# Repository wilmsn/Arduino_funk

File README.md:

# Arduino_funk
A simple PCB for ATMEGA328 and nrf24l01

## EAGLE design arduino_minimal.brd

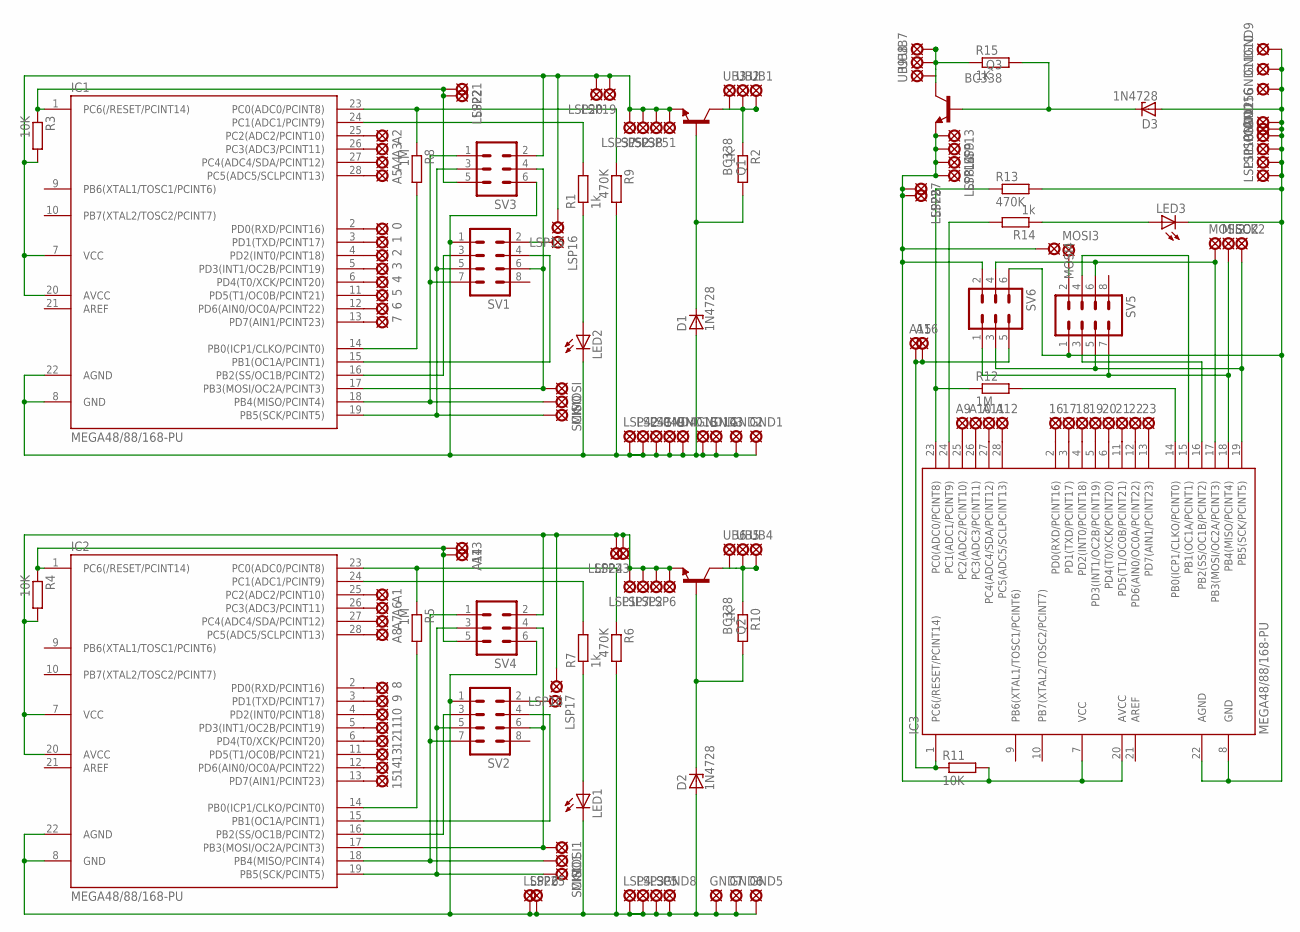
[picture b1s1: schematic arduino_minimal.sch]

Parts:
0, 1, 2, 3, 4, 5, 6, 7, 8, 9, 10, 11, 12, 13, 14, 15, 16, 17, 18, 19, 20, 21, 22, 23: LSP10
A1, A2, A3, A4, A5, A6, A7, A8, A9, A10, A11, A12, A13, A14, A15, A16: LSP10
D1, D2, D3: 1N4728; DO41Z10
GND1, GND2, GND3, GND4, GND5, GND6, GND7, GND8, GND9, GND10, GND11, GND12, GND13, GND14, GND15, GND16: LSP10
IC1, IC2, IC3: MEGA48/88/168-PU; DIL28-3
LED1, LED2, LED3: LED3MM
LSP1, LSP2, LSP3, LSP4, LSP5, LSP6, LSP7, LSP8, LSP9, LSP10, LSP11, LSP12, LSP13, LSP14, LSP15, LSP16, LSP17, LSP18, LSP19, LSP20, LSP21, LSP22, LSP23, LSP24, LSP25, LSP26, LSP27, LSP28, LSP37, LSP38, LSP41, LSP42, LSP49, LSP51, LSP52: LSP10
MISO, MISO1, MISO2: LSP10
MOSI, MOSI1, MOSI2, MOSI3, MOSI4: LSP10
Q1, Q2, Q3: BC338; TO92-EBC
R1, R7, R14: 1k; 0204/7
R2, R10, R15: 1K; 0204/7
R3, R4, R11: 10K; 0204/7
R5, R8, R12: 1M; 0204/7
R6, R9, R13: 470K; 0204/7
SCK, SCK1, SCK2: LSP10
SV1, SV2, SV5: MA04-2
SV3, SV4, SV6: MA03-2
UB1, UB2, UB3, UB4, UB5, UB6, UB7, UB8, UB9: LSP10

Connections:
CE1: IC1.16 (PB2(SS/OC1B/PCINT2)), SV1.3
CSN1: IC1.15 (PB1(OC1A/PCINT1)), SV1.4
GND: D1.A, GND1.MP, GND2.MP, GND3.MP, GND4.MP, GND13.MP, GND14.MP, IC1.8 (GND), IC1.22 (AGND), LED2.K (C), LSP41.MP, LSP42.MP, LSP49.MP, R9.2, SV1.1, SV3.6
MISO1: IC1.18 (PB4(MISO/PCINT4)), MISO.MP, SV1.7, SV3.1
MOSI1: IC1.17 (PB3(MOSI/OC2A/PCINT3)), MOSI.MP, SV1.6, SV3.4
unnamed: A13.MP, A14.MP, IC2.1 (PC6(/RESET/PCINT14)), R4.1, SV4.5
unnamed: LSP16.MP, SV1.2
unnamed: IC1.14 (PB0(ICP1/CLKO/PCINT0)), R8.2
unnamed: IC2.14 (PB0(ICP1/CLKO/PCINT0)), R5.2
unnamed: IC1.23 (PC0(ADC0/PCINT8)), R8.1, R9.1
unnamed: IC2.23 (PC0(ADC0/PCINT8)), R5.1, R6.1
unnamed: IC2.24 (PC1(ADC1/PCINT9)), R7.2
unnamed: LED1.A, R7.1
unnamed: IC1.24 (PC1(ADC1/PCINT9)), R1.2
unnamed: LED2.A, R1.1
unnamed: IC2.15 (PB1(OC1A/PCINT1)), SV2.4
unnamed: IC2.16 (PB2(SS/OC1B/PCINT2)), SV2.3
unnamed: IC2.17 (PB3(MOSI/OC2A/PCINT3)), MOSI1.MP, SV2.6, SV4.4
unnamed: IC2.18 (PB4(MISO/PCINT4)), MISO1.MP, SV2.7, SV4.1
unnamed: IC2.19 (PB5(SCK/PCINT5)), SCK1.MP, SV2.5, SV4.3
unnamed: LSP17.MP, SV2.2
unnamed: MOSI3.MP, SV5.2
unnamed: 15.MP, IC2.13 (PD7(AIN1/PCINT23))
unnamed: 14.MP, IC2.12 (PD6(AIN0/OC0A/PCINT22))
unnamed: 13.MP, IC2.11 (PD5(T1/OC0B/PCINT21))
unnamed: 12.MP, IC2.6 (PD4(T0/XCK/PCINT20))
unnamed: 11.MP, IC2.5 (PD3(INT1/OC2B/PCINT19))
unnamed: 10.MP, IC2.4 (PD2(INT0/PCINT18))
unnamed: 9.MP, IC2.3 (PD1(TXD/PCINT17))
unnamed: 8.MP, IC2.2 (PD0(RXD/PCINT16))
unnamed: A1.MP, IC2.25 (PC2(ADC2/PCINT10))
unnamed: A6.MP, IC2.26 (PC3(ADC3/PCINT11))
unnamed: A7.MP, IC2.27 (PC4(ADC4/SDA/PCINT12))
unnamed: A8.MP, IC2.28 (PC5(ADC5/SCLPCINT13))
unnamed: 7.MP, IC1.13 (PD7(AIN1/PCINT23))
unnamed: 6.MP, IC1.12 (PD6(AIN0/OC0A/PCINT22))
unnamed: 5.MP, IC1.11 (PD5(T1/OC0B/PCINT21))
unnamed: 4.MP, IC1.6 (PD4(T0/XCK/PCINT20))
unnamed: 3.MP, IC1.5 (PD3(INT1/OC2B/PCINT19))
unnamed: 2.MP, IC1.4 (PD2(INT0/PCINT18))
unnamed: 1.MP, IC1.3 (PD1(TXD/PCINT17))
unnamed: 0.MP, IC1.2 (PD0(RXD/PCINT16))
unnamed: A2.MP, IC1.25 (PC2(ADC2/PCINT10))
unnamed: A3.MP, IC1.26 (PC3(ADC3/PCINT11))
unnamed: A4.MP, IC1.27 (PC4(ADC4/SDA/PCINT12))
unnamed: A5.MP, IC1.28 (PC5(ADC5/SCLPCINT13))
unnamed: D2.A, GND5.MP, GND6.MP, GND7.MP, GND8.MP, IC2.8 (GND), IC2.22 (AGND), LED1.K (C), LSP3.MP, LSP4.MP, LSP5.MP, LSP25.MP, LSP26.MP, R6.2, SV2.1, SV4.6
unnamed: Q1.C, R2.1, UB1.MP, UB2.MP, UB3.MP
unnamed: D1.C, Q1.B, R2.2
unnamed: Q2.C, R10.1, UB4.MP, UB5.MP, UB6.MP
unnamed: D2.C, Q2.B, R10.2
unnamed: A15.MP, A16.MP, IC3.1 (PC6(/RESET/PCINT14)), R11.1, SV6.5
unnamed: IC3.14 (PB0(ICP1/CLKO/PCINT0)), R12.2
unnamed: IC3.23 (PC0(ADC0/PCINT8)), R12.1, R13.1
unnamed: IC3.24 (PC1(ADC1/PCINT9)), R14.2
unnamed: LED3.A, R14.1
unnamed: IC3.15 (PB1(OC1A/PCINT1)), SV5.4
unnamed: IC3.16 (PB2(SS/OC1B/PCINT2)), SV5.3
unnamed: IC3.17 (PB3(MOSI/OC2A/PCINT3)), MOSI2.MP, SV5.6, SV6.4
unnamed: IC3.18 (PB4(MISO/PCINT4)), MISO2.MP, SV5.7, SV6.1
unnamed: IC3.19 (PB5(SCK/PCINT5)), SCK2.MP, SV5.5, SV6.3
unnamed: 23.MP, IC3.13 (PD7(AIN1/PCINT23))
unnamed: 22.MP, IC3.12 (PD6(AIN0/OC0A/PCINT22))
unnamed: 21.MP, IC3.11 (PD5(T1/OC0B/PCINT21))
unnamed: 20.MP, IC3.6 (PD4(T0/XCK/PCINT20))
unnamed: 19.MP, IC3.5 (PD3(INT1/OC2B/PCINT19))
unnamed: 18.MP, IC3.4 (PD2(INT0/PCINT18))
unnamed: 17.MP, IC3.3 (PD1(TXD/PCINT17))
unnamed: 16.MP, IC3.2 (PD0(RXD/PCINT16))
unnamed: A9.MP, IC3.25 (PC2(ADC2/PCINT10))
unnamed: A10.MP, IC3.26 (PC3(ADC3/PCINT11))
unnamed: A11.MP, IC3.27 (PC4(ADC4/SDA/PCINT12))
unnamed: A12.MP, IC3.28 (PC5(ADC5/SCLPCINT13))
unnamed: D3.A, GND9.MP, GND10.MP, GND11.MP, GND12.MP, GND15.MP, GND16.MP, IC3.8 (GND), IC3.22 (AGND), LED3.K (C), LSP10.MP, LSP11.MP, LSP12.MP, R13.2, SV5.1, SV6.6
unnamed: Q3.C, R15.1, UB7.MP, UB8.MP, UB9.MP
unnamed: D3.C, Q3.B, R15.2
RES: IC1.1 (PC6(/RESET/PCINT14)), LSP21.MP, LSP22.MP, R3.1, SV3.5
SCK1: IC1.19 (PB5(SCK/PCINT5)), SCK.MP, SV1.5, SV3.3
VCC: IC1.7 (VCC), IC1.20 (AVCC), LSP15.MP, LSP19.MP, LSP20.MP, LSP37.MP, LSP38.MP, LSP51.MP, LSP52.MP, Q1.E, R3.2, SV3.2
VCC1: IC2.7 (VCC), IC2.20 (AVCC), LSP1.MP, LSP2.MP, LSP6.MP, LSP7.MP, LSP18.MP, LSP23.MP, LSP24.MP, Q2.E, R4.2, SV4.2
VCC2: IC3.7 (VCC), IC3.20 (AVCC), LSP8.MP, LSP9.MP, LSP13.MP, LSP14.MP, LSP27.MP, LSP28.MP, MOSI4.MP, Q3.E, R11.2, SV6.2

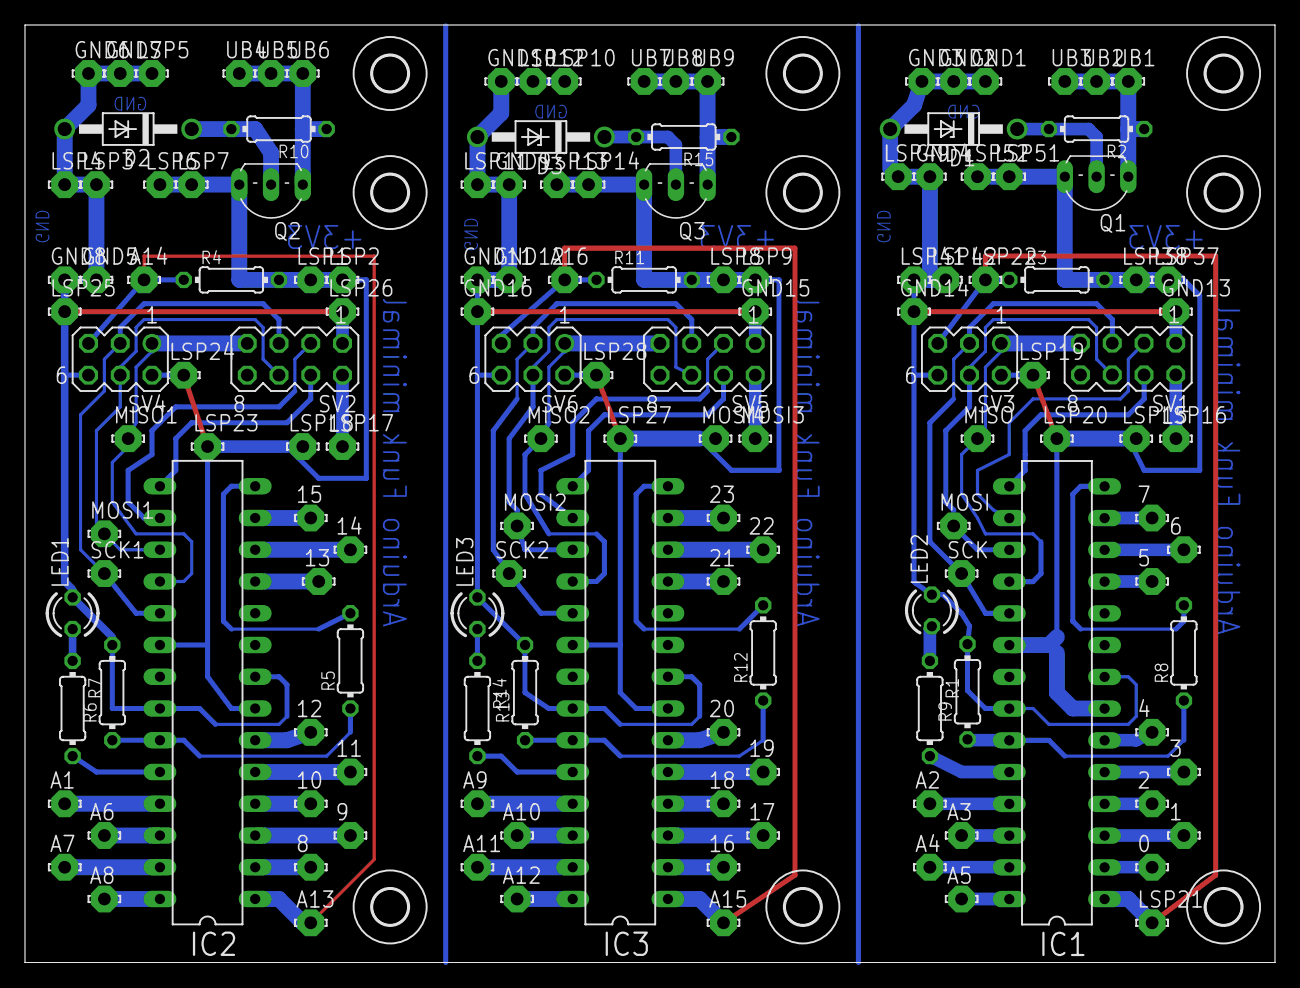
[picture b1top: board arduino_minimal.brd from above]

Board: 2 copper layers, 100.0 x 75.0 mm, 153 parts (0 on the bottom side), 81 nets.

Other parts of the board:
U$1, U$2, U$3, U$4, U$5, U$6, U$7, U$8, U$9: 2,8

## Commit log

2015-02-08 initial Version
